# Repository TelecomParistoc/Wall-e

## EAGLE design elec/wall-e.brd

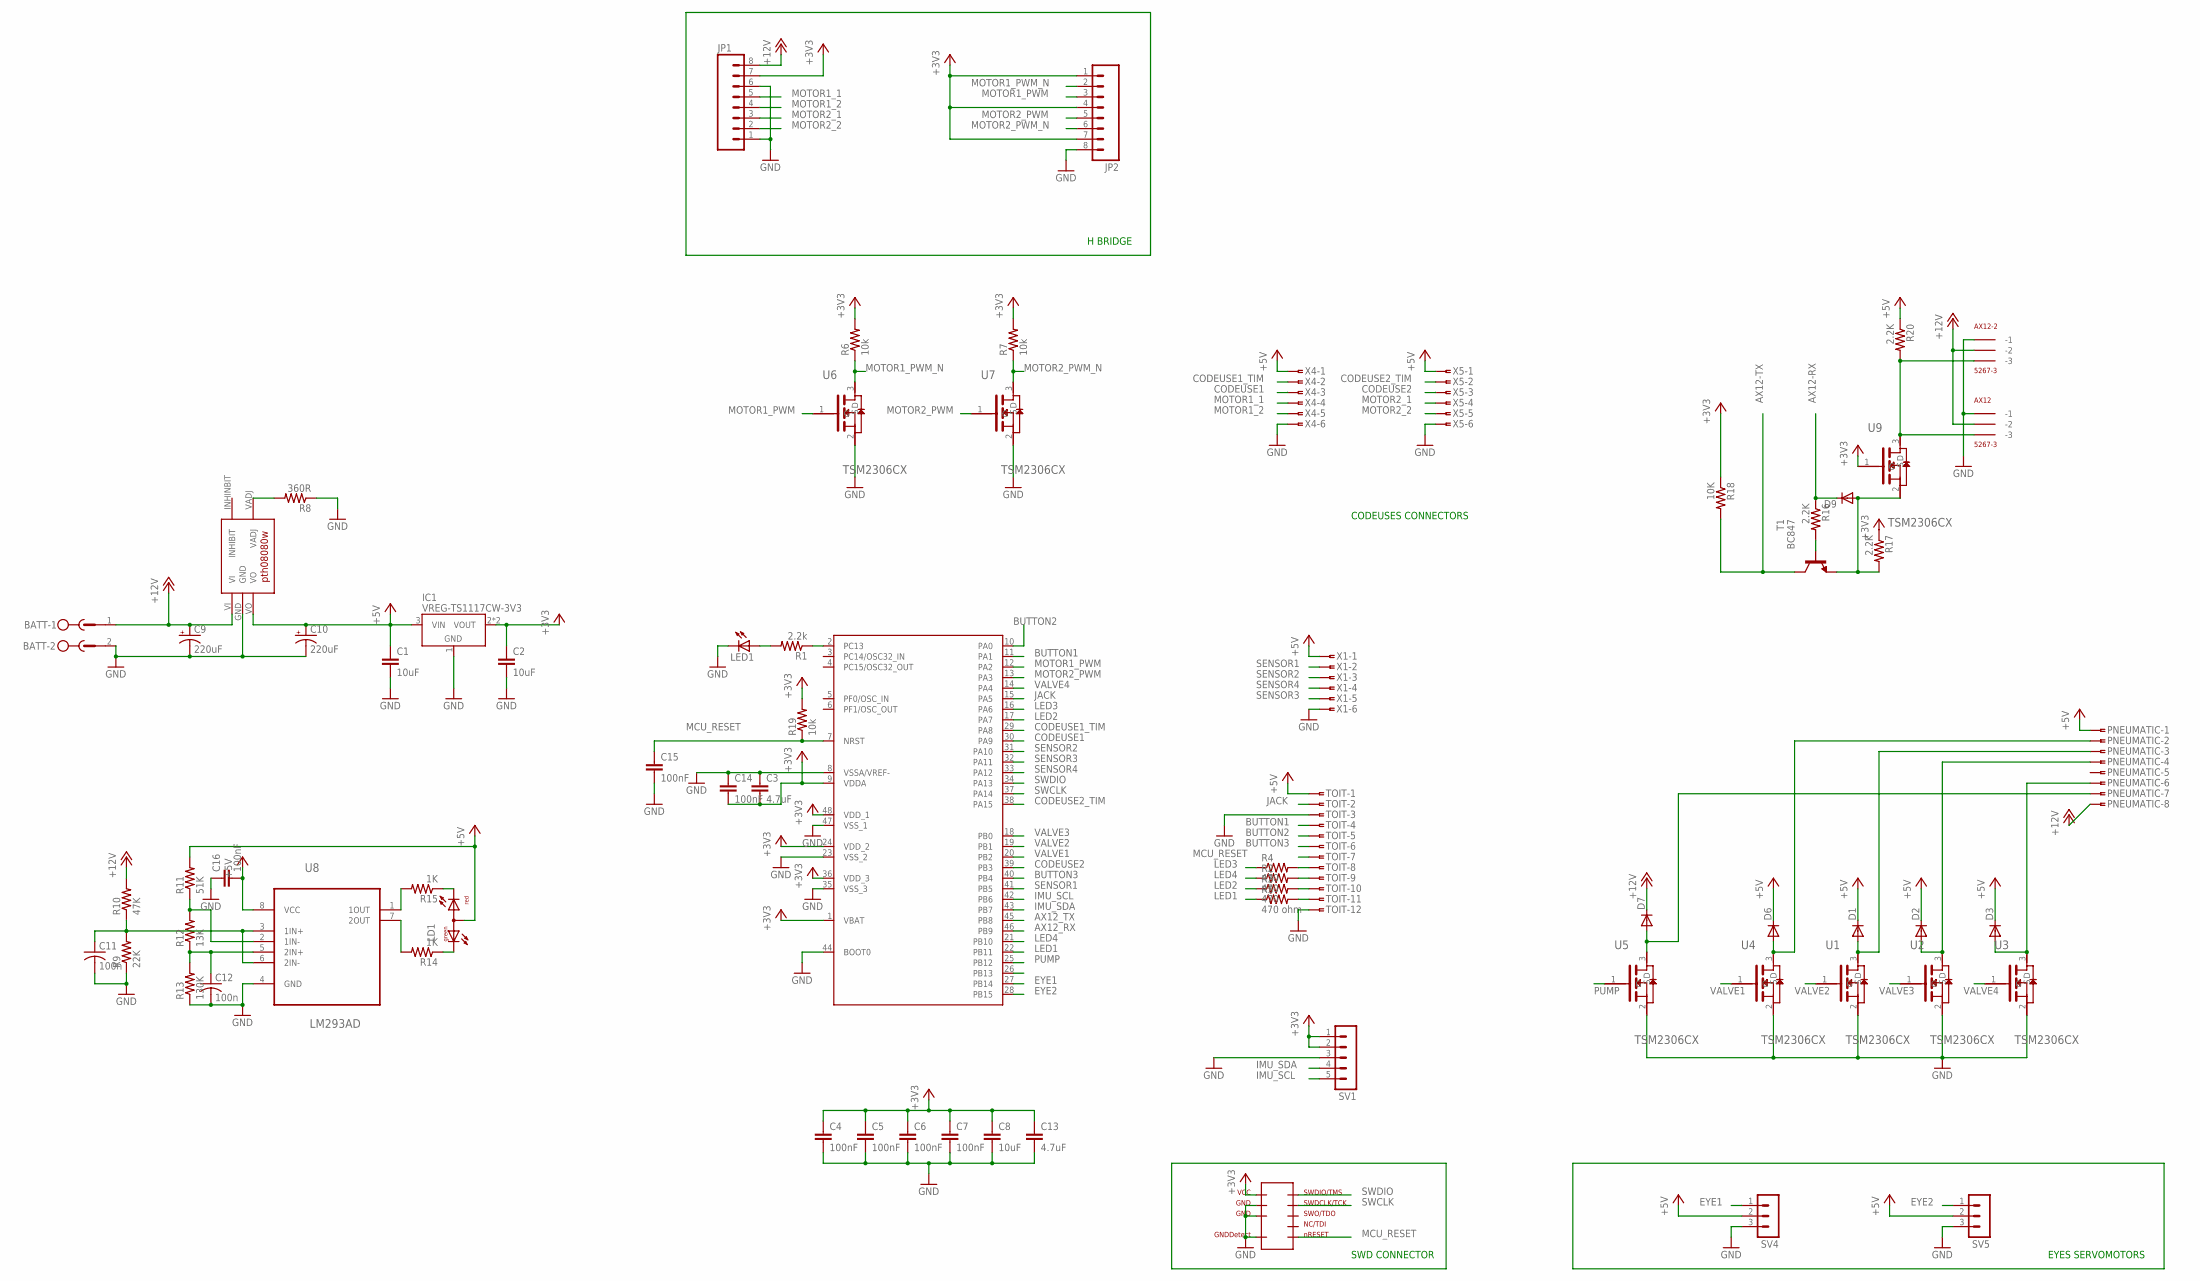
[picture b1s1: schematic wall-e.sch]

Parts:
AX12, AX12-2: 5267-3
BATT: MSTBV2
C1, C2, C8: 10uF; C0805
C3, C13: 4.7uF; C0805
C4, C5, C6, C7, C14, C15, C16: 100nF; C0805
C9: 220uF; E3,5-8
C10: 220uF; E2,5-7
C11, C12: 100n; C0805
D1, D2, D3, D6, D7: DIODE-SOD323-R; SOD323-R
D9: DIODE-SOD523; SOD523
IC1: VREG-TS1117CW-3V3; SOT223
JP1, JP2: M08LONGPADS; 1X08_LONGPADS
LD1: DUOLED-RG-A; DUOLED-A-5MM
LED1: LEDCHIP-LED0805; CHIP-LED0805
PNEUMATIC: SMDTOP-8; SMDTOP8
R1: 2.2k; R0805
R2, R3, R4: 470; R0805
R5: 470 ohm; R0805
R6, R7, R19: 10k; R0805
R8: 360R; R0805
R9: 22K; R0805
R10: 47K; R0805
R11: 51K; R0805
R12: 13K; R0805
R13: 130K; R0805
R14, R15: 1K; R0805
R16, R17, R20: 2.2K; R0805
R18: 10K; R0805
SV1: MA05-1
SV4, SV5: MA03-1
T1: BC847; SOT23
TOIT: SMDTOP-12; SMDTOP12
U1, U2, U3, U4, U5, U6, U7, U9: TSM2306CX; SOT95P280X130-3N
U8: LM293AD; SOIC127P600X175-8N
U$1: STM32F301C8; TQFP48
U$2: REGUL_PTH
U$3: SWD/JTAG-_PINS; SAMTEC_SHF-105-01-L-D-SM
X1, X4, X5: SMDTOP-6; SMDTOP6

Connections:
+3V3: C2.1, C3.2, C4.1, C5.1, C6.1, C7.1, C8.1, C13.1, C14.2, IC1.2 (VOUT), IC1.4 (VOUT), JP1.7, JP2.1, JP2.4, JP2.7, R6.2, R7.2, R17.1, R18.1, R19.2, SV1.1, SV1.2, U9.1 (G), U$1.1 (VBAT), U$1.9 (VDDA), U$1.24 (VDD_2), U$1.36 (VDD_3), U$1.48 (VDD_1), U$3.P$1
+5V: C1.1, C10.+, C16.2, D1.C, D2.C, D3.C, D6.C, IC1.3 (VIN), LD1.A, PNEUMATIC.1, R11.2, R20.1, SV4.2, SV5.2, TOIT.1, U8.8 (VCC), U$2.VO, X1.1, X4.1, X5.1
+12V: AX12.P$2 (-2), AX12-2.P$2 (-2), BATT.1, C9.+, D7.C, JP1.8, PNEUMATIC.8, R10.2, U$2.VI
AX12-RX: D9.C, R16.1
AX12-TX: R18.2, T1.3 (C)
AX12_RX: U$1.46 (PB9)
AX12_TX: U$1.45 (PB8)
BUTTON1: TOIT.4, U$1.11 (PA1)
BUTTON2: TOIT.5, U$1.10 (PA0)
BUTTON3: TOIT.6, U$1.40 (PB4)
CODEUSE1: U$1.30 (PA9), X4.3
CODEUSE1_TIM: U$1.29 (PA8), X4.2
CODEUSE2: U$1.39 (PB3), X5.3
CODEUSE2_TIM: U$1.38 (PA15), X5.2
EYE1: SV4.1, U$1.27 (PB14)
EYE2: SV5.1, U$1.28 (PB15)
GND: AX12.P$1 (-1), AX12-2.P$1 (-1), BATT.2, C1.2, C2.2, C3.1, C4.2, C5.2, C6.2, C7.2, C8.2, C9.-, C10.-, C11.2, C12.2, C13.2, C14.1, C15.2, C16.1, IC1.1 (GND), JP1.1, JP1.6, JP2.8, LED1.C, R8.1, R9.1, R13.1, SV1.3, SV4.3, SV5.3, TOIT.3, TOIT.12, U1.2 (S), U2.2 (S), U3.2 (S), U4.2 (S), U5.2 (S), U6.2 (S), U7.2 (S), U8.4 (GND), U$1.8 (VSSA/VREF-), U$1.23 (VSS_2), U$1.35 (VSS_3), U$1.44 (BOOT0), U$1.47 (VSS_1), U$2.GND, U$3.P$3, U$3.P$5, U$3.P$9, X1.6, X4.6, X5.6
IMU_SCL: SV1.5, U$1.42 (PB6)
IMU_SDA: SV1.4, U$1.43 (PB7)
JACK: TOIT.2, U$1.15 (PA5)
LED1: R5.1, U$1.22 (PB11)
LED2: R3.1, U$1.17 (PA7)
LED3: R4.1, U$1.16 (PA6)
LED4: R2.1, U$1.21 (PB10)
MCU_RESET: C15.1, R19.1, TOIT.7, U$1.7 (NRST), U$3.P$10
MOTOR1_1: JP1.5, X4.4
MOTOR1_2: JP1.4, X4.5
MOTOR1_PWM: JP2.3, U6.1 (G), U$1.12 (PA2)
MOTOR1_PWM_N: JP2.2, R6.1, U6.3 (D)
MOTOR2_1: JP1.3, X5.4
MOTOR2_2: JP1.2, X5.5
MOTOR2_PWM: JP2.5, U7.1 (G), U$1.13 (PA3)
MOTOR2_PWM_N: JP2.6, R7.1, U7.3 (D)
unnamed: R5.2, TOIT.11
unnamed: R3.2, TOIT.10
unnamed: R2.2, TOIT.9
unnamed: R4.2, TOIT.8
unnamed: D1.A, PNEUMATIC.3, U1.3 (D)
unnamed: D2.A, PNEUMATIC.4, U2.3 (D)
unnamed: D3.A, PNEUMATIC.6, U3.3 (D)
unnamed: D6.A, PNEUMATIC.2, U4.3 (D)
unnamed: D7.A, PNEUMATIC.7, U5.3 (D)
unnamed: R1.1, U$1.2 (PC13)
unnamed: R8.2, U$2.VADJ
unnamed: R15.2, U8.1 (1OUT)
unnamed: LD1.CR, R15.1
unnamed: R14.2, U8.7 (2OUT)
unnamed: LD1.CX (CG), R14.1
unnamed: LED1.A, R1.2
unnamed: C11.1, R9.2, R10.1, U8.3 (1IN+), U8.6 (2IN-)
unnamed: R11.1, R12.2, U8.2 (1IN-)
unnamed: C12.1, R12.1, R13.2, U8.5 (2IN+)
unnamed: AX12.P$3 (-3), AX12-2.P$3 (-3), R20.2, U9.3 (D)
unnamed: R16.2, T1.1 (B)
unnamed: D9.A, R17.2, T1.2 (E), U9.2 (S)
PUMP: U5.1 (G), U$1.25 (PB12)
SENSOR1: U$1.41 (PB5), X1.2
SENSOR2: U$1.31 (PA10), X1.3
SENSOR3: U$1.32 (PA11), X1.5
SENSOR4: U$1.33 (PA12), X1.4
SWCLK: U$1.37 (PA14), U$3.P$4
SWDIO: U$1.34 (PA13), U$3.P$2
VALVE1: U4.1 (G), U$1.20 (PB2)
VALVE2: U1.1 (G), U$1.19 (PB1)
VALVE3: U2.1 (G), U$1.18 (PB0)
VALVE4: U3.1 (G), U$1.14 (PA4)

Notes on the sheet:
SWD CONNECTOR
H BRIDGE
CODEUSES CONNECTORS
EYES SERVOMOTORS

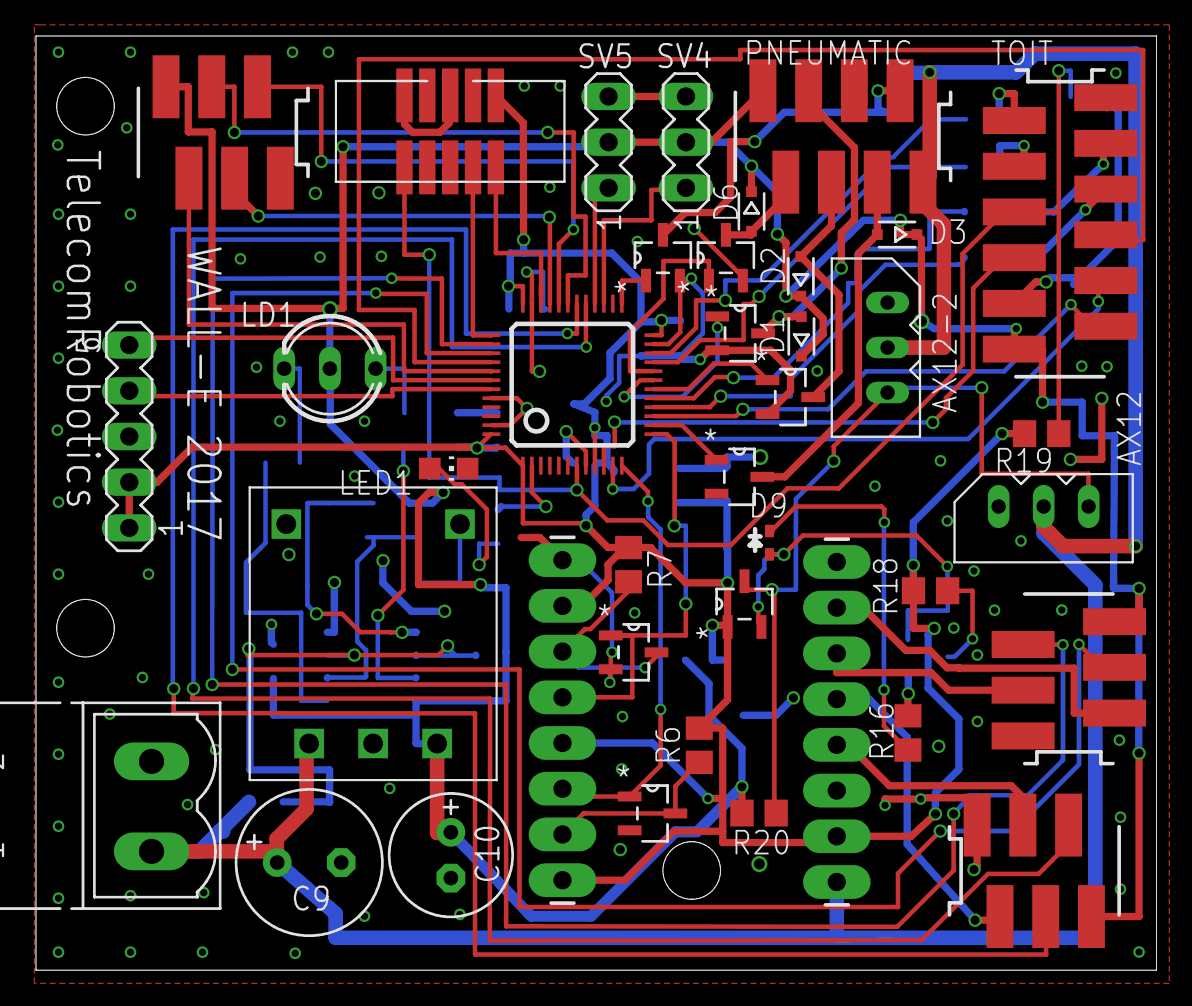
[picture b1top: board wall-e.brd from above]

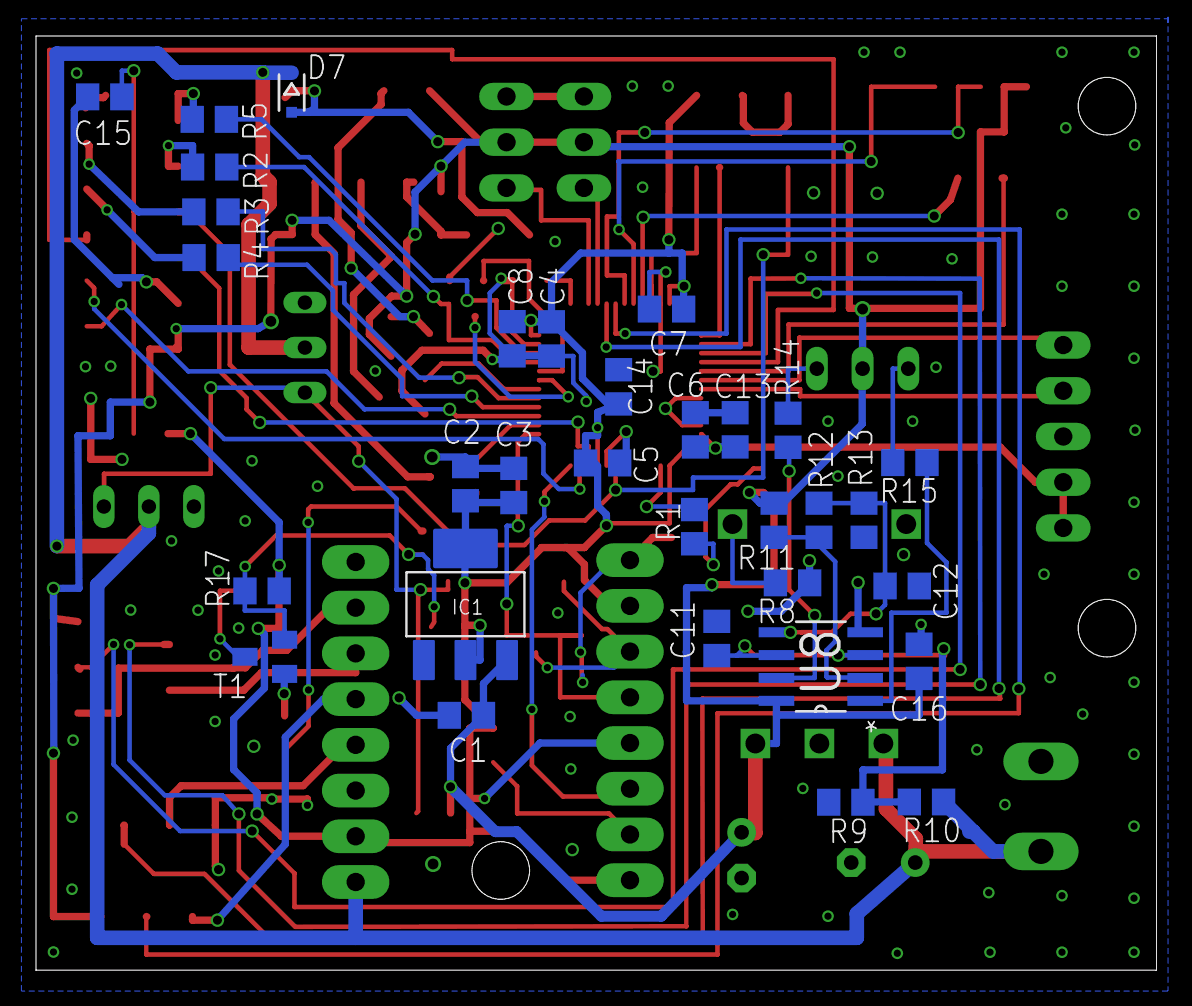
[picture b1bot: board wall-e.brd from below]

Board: 2 copper layers, 62.2 x 51.9 mm, 71 parts (32 on the bottom side), 64 nets.

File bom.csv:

Qty;Qty to buy;Value;Device;Package;Parts;Distributor
1;0;;DIODE-SOD523;SOD523;D9;
1;0;;DUOLED-RG-A;DUOLED-A-5MM;LD1;
1;0;;LEDCHIP-LED0805;CHIP-LED0805;LED1;
2;0;;M08LONGPADS;1X08_LONGPADS;JP1, JP2;
2;0;;MA03-1;MA03-1;SV4, SV5;
1;0;;MA05-1;MA05-1;SV1;
1;0;;MSTBV2;MSTBV2;BATT;
1;0;;SMDTOP-8;SMDTOP8;PNEUMATIC;
2;0;100n;C-USC0805;C0805;C11, C12;
7;0;100nF;C-EUC0805;C0805;C4, C5, C6, C7, C15, C16;
1;0;10K;R-US_R0805;R0805;R18;
3;0;10k;R-US_R0805;R0805;R6, R7, R19;
1;0;130K;R-US_R0805;R0805;R13;
1;0;13K;R-US_R0805;R0805;R12;
2;0;1K;R-US_R0805;R0805;R14, R15;
3;0;2.2K;R-US_R0805;R0805;R16, R17, R20;
1;0;2.2k;R-US_R0805;R0805;R1;
1;0;100uF;CPOL-USE2.5-7;E2,5-7;C10;
1;0;22K;R-US_R0805;R0805;R9;
1;0;360R;R-US_R0805;R0805;R8;
3;0;470;R-US_R0805;R0805;R2, R3, R4;
1;0;470 ohm;R-US_R0805;R0805;R5;
1;0;47K;R-US_R0805;R0805;R10;
1;0;51K;R-US_R0805;R0805;R11;
1;0;BC847;BC847;SOT23;T1;
1;0;LM293AD;LM293AD;SOIC127P600X175-8N;U8;
1;1;;SMDTOP-12;SMDTOP12;TOIT;MOUSER 571-1-215083-2, FARNELL 2473361
1;1;;STM32F301C8;TQFP48;U$1;MOUSER 511-STM32F301C8T6
1;1;100uF;CPOL-USE3.5-8;E3,5-8;C9;FARNELL 1219478
2;2;4.7uF;C-EUC0805;C0805;C13, C3;FARNELL 1759420
1;1;REGUL_PTH;REGUL_PTH;REGUL_PTH;U$2;FARNELL 2383158
1;1;SWD/JTAG-_PINS;SWD/JTAG-_PINS;SAMTEC_SHF-105-01-L-D-SM;U$3;FARNELL 1885915
1;1;NCP1117;NCP1117;SOT223;IC1;MOUSER 863-NCP1117LPST33T3G 
2;2;5267-3;5267-3;5267-3;AX12, AX12-2;FARNELL 9979620
3;3;;SMDTOP-6;SMDTOP6;X1, X4, X5;FARNELL 2473376, FARNELL 2473358
3;3;10uF;C-EUC0805;C0805;C1, C2, C8;FARNELL 2320856
5;5;;DIODE-SOD323-R;SOD323-R;D1, D2, D3, D6, D7;FARNELL 2528898
8;8;TSM2306CX;TSM2306CX;SOT95P280X130-3N;U1, U2, U3, U4, U5, U6, U7, U9;FARNELL 1864577 (remplacé par 2473358 )

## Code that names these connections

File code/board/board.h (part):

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/*
 * GPIOA setup:
 *
 * PA0  - BUTTON_2                  (input floating).
 * PA1  - BUTTON_1                  (input floating).
 * PA2  - MOTOR_1_PWM               (alternate 9).
 * PA3  - MOTOR_2_PWM               (alternate 9).
 * PA4  - VALVE_4                   (output push-pull).
 * PA5  - JACK                      (input floating).
 * PA6  - LED_3                     (output push-pull).
 * PA7  - LED_2                     (output push-pull).
 * PA8  - CODEUSE_1_TIM             (input floating).
 * PA9  - CODEUSE_1                 (input floating).
 * PA10 - SENSOR_2                  (input floating).
 * PA11 - SENSOR_3                  (input floating).
 * PA12 - SENSOR_4                  (input floating).
 * PA13 - SWDIO                     (alternate 0 pull-up).
 * PA14 - SWCLK                     (alternate 0 pull-down).
 * PA15 - CODEUSE_2_TIM             (input floating).
 */
#define VAL_GPIOA_MODER             (PIN_MODE_INPUT(GPIOA_BUTTON_2) |       \
                                     PIN_MODE_INPUT(GPIOA_BUTTON_1) |       \
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/*
 * GPIOB setup:
 *
 * PB0  - VALVE_3                   (output push-pull).
 * PB1  - VALVE_2                   (output push-pull).
 * PB2  - VALVE_1                   (output push-pull).
 * PB3  - CODEUSE_2                 (input floating).
 * PB4  - BUTTON_3                  (input floating).
 * PB5  - SENSOR_1                  (input floating).
 * PB6  - IMU_PROC_TX               (alternate 4).
 * PB7  - IMU_PROC_RX               (alternate 4).
 * PB8  - AX12_TX                   (alternate 7).
 * PB9  - AX12_RX                   (alternate 7).
 * PB10 - LED_4                     (output push-pull).
 * PB11 - LED_1                     (output push-pull).
 * PB12 - PUMP                      (output push-pull).
 * PB13 - PIN13                     (input floating).
 * PB14 - EYE_START                 (input floating).
 * PB15 - EYE2                      (alternate 1).
 */
#define VAL_GPIOB_MODER             (PIN_MODE_OUTPUT(GPIOB_VALVE_3) |       \
                                     PIN_MODE_OUTPUT(GPIOB_VALVE_2) |       \
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/*
 * GPIOC setup:
 *
 * PC13 - DEBUG_LED                 (output push-pull).
 * PC14 - PIN14                     (input floating).
 * PC15 - PIN15                     (input floating).
 */
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
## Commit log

2017-01-12 Addition of the component list
2017-01-19 Addiiton of pin allocation of STM32F301 48 pins
2017-01-19 Allocation of the pins
2017-01-26 Beginnig of the schematic.
2017-02-03 Second part of the schematic
2017-02-17 Addition of connectors to control the motors.
2017-02-17 SWD and decoupling capa
2017-02-17 STM32 library (improved version of a cadsoft library)
2017-02-24 Addition of the AX12 control circuit and battery manager
2017-02-24 Cleaning of the schematic
2017-02-24 Library with SWD connector
2017-02-24 Addition of the project description file
2017-02-26 Improvement of the SWD connector in the library
2017-02-26 Addition of the JTAG device
2017-02-27 Update of the SWD connector
2017-02-27 Creation of the board
2017-03-05 Corrections following Arnaud's advices.
2017-03-06 Correction of some errors (capa size and RX/TX pinout)
2017-03-06 Correction of the board
2017-03-06 Change in the H bridge
2017-03-07 Last corrections on the schematic
2017-03-07 Placement of the decoupling capacitor
2017-03-07 Placement of main components
2017-03-09 Placement
2017-03-10 Better allocation of the pins
2017-03-10 Routing
2017-03-10 Update of the routing table
2017-03-13 First DRC
2017-03-14 Correction of the DRC errors
2017-03-15 Some corrections
2017-03-15 Minor corrections
2017-03-15 Corrections
2017-03-16 Improvement of silkscreen
2017-03-16 Addition of board name
2017-03-19 WIP small board fixes and BOM
2017-03-19 added distributor references
2017-03-19 Small modification
2017-03-20 fixed board
2017-03-21 Minor changes
2017-03-23 Addition of pdf versions
2017-04-03 Correction of a defect found by eurocircuit (useless trace)
2017-05-07 Cleaning
2017-05-07 Addition of ChibiOS as submodule
2017-05-07 Bring-up
2017-05-07 Addition of STMdrivers as submodule
2017-05-08 Motor control
2017-05-24 Addition of pneumatic functions
2017-05-24 Addition of functions to manage the roof
2017-05-25 Wall-e can now move forward
2017-05-26 Wall-e is now moving (but not enough for homologation)
2017-05-26 Homologation code
2017-12-10 Addition of a gitignore
2017-12-10 Addition of IMU
2018-02-04 Microcontroller changed, memory reduced to 32kb
2018-02-04 Test for arms
2018-02-04 Addition of libAX12
2018-02-11 Test for AX12
2018-02-11 Addition of eyes control
2018-03-24 Add UART protocol for IMU
2018-03-31 Update libAX12 submodule
2018-04-21 Eyes improvements
2018-05-05 Add obstacle avoidance and clean oode
2018-05-06 OK for homologation
2018-05-09 Cubes OK
2018-05-11 doesn't work
2019-05-29 Test for 2019
2019-05-29 Fix in case of obstacle detection
2019-05-30 Fix issue in movement when obstacle detected
2019-05-30 Reduce angle for position ARMS_UP
2019-05-30 Add .gdbinit
2019-05-30 Increase movement druration to be sure to hit the button
